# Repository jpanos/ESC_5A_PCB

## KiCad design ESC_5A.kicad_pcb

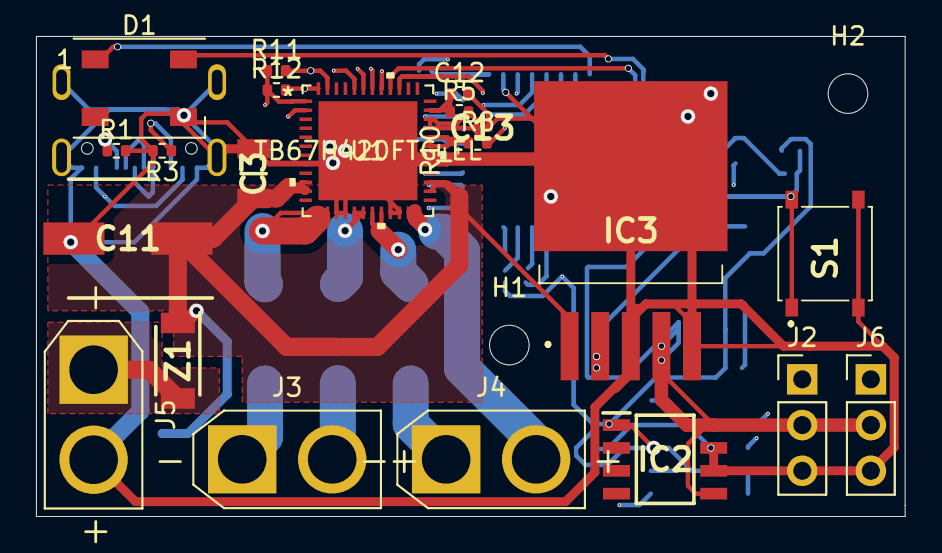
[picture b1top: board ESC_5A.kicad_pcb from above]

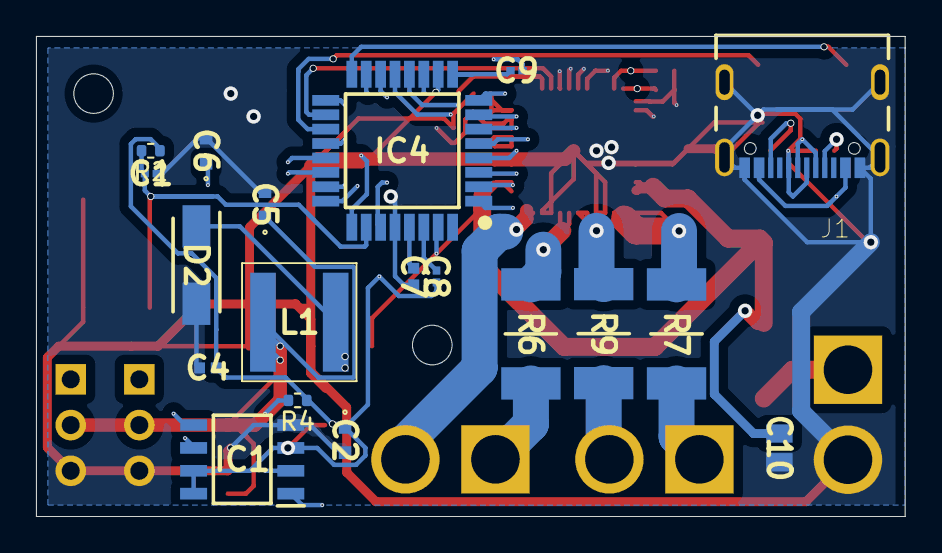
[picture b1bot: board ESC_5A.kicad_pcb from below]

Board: 4 copper layers, 48.3 x 26.7 mm, 43 parts (19 on the bottom side), 41 nets.

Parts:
C1, C8, C9, C13: .1uF; CAPC0603X33N
C2, C5, C6: 10uF; C1608_Commercial
C3: 10uF; CAPC3216X180N
C4, C7: 1uF; CAPC1005X55N
C10: .1uF; CAPC2012X110N
C11: 100uF; CAPAE660X800N
C12: 270pF; C_0402_1005Metric
D1: WS2812B; LED_WS2812B_PLCC4_5.0x5.0mm_P3.2mm
D2: B340AE-13; DIOM5226X240N
H1, H2: MountingHole; MountingHole_2.2mm_M2
IC1: EEPROM; SOIC127P600X175-8N
IC2: 3.3V Reg; SOIC127P600X170-8N
IC3: 5V_Reg; AP1501A50K5G13
IC4: ATSAMD21E17D-AUT; QFP80P900X900X120-32N
J1: USBc; GCT_USB4105-GF-A
J2, J6: 5V_PWR; PinHeader_1x03_P2.54mm_Vertical
J3: M1; AMASS_XT30U-M_1x02_P5.0mm_Vertical
J4: M2; AMASS_XT30U-M_1x02_P5.0mm_Vertical
J5: PWR_IN; AMASS_XT30U-M_1x02_P5.0mm_Vertical
L1: 33uH; XAL6060333MEC
R1, R3, R4, R5: 5.1k; R_0402_1005Metric
R2: 100k; R_0402_1005Metric
R6, R7, R9: .01; RESC6430X66N
R8: 20k; R_0402_1005Metric
R10: 5k; R_0402_1005Metric
R11, R12: 10k; R_0402_1005Metric
S1: PTS526_SK15_SMTR2_LFS; PTS526SK15SMTR2LFS
U1: TB67H420FTG_EL
Z1: SZMMSZ4713T1G; SODFL4724X108N

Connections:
+3V3: C2.1, C4.1, C8.1, C9.1, IC1.3, IC1.7, IC1.8, IC2.1, R2.1, R4.1
+5V: C5.1, C6.1, IC2.5, IC2.8, IC3.4, J1.A4_B9, J1.B4_A9, J2.2, J6.2, L1.2
ADC_1: IC4.8, J3.1, R7.2
ADC_2: IC4.6, J4.1, R6.2
ADC_3: IC4.7, J3.2, R9.2
ADC_MUX_GND: IC4.3, R9.1, U1.17, U1.18
ADC_VREFA: IC4.4, R7.1, U1.13, U1.14
ADC_VREFB: IC4.5, R6.1, U1.19, U1.20
CS_EEPROM: IC1.1, IC4.11, R4.2
D+: IC4.24, J1.A6, J1.B6
D-: IC4.23, J1.A7, J1.B7
GND: C1.1, C2.2, C3.2, C4.2, C5.2, C6.2, C7.2, C10.2, C11.2, C12.2, C13.1, D1.3, D2.2, IC1.4, IC2.6, IC2.7, IC3.3, IC3.5, IC3.6, IC4.10, IC4.28, J1.A1_B12, J1.B1_A12, J1.S1, J1.S2, J1.S3, J1.S4, J2.3, J5.2, J6.3, R1.2, R3.2, R10.1, S1.3, S1.4, U1.8, U1.15, U1.16, U1.21, U1.22, U1.29, U1.30, U1.49
HBMODE: IC4.25, U1.2
INA1: IC4.15, U1.41
INA2: IC4.14, U1.42
INB1: IC4.13, U1.43
INB2: IC4.12, U1.44
LO1: IC4.1, R11.2, U1.47
LO2: IC4.2, R12.2, U1.48
MISO_EEPROM: IC1.2, IC4.20
MOSI_EEPROM: IC1.5, IC4.22
MotorB_Neg: J4.2, U1.23, U1.24
NRST: C1.2, IC4.26, R2.2, S1.1, S1.2
unnamed: C7.1, IC4.29
unnamed: C8.2, IC4.30
unnamed: C9.2, IC4.9
unnamed: D2.1, IC3.2, L1.1
unnamed: J1.A5, R1.1
unnamed: J1.B5, R3.1
OSCM: C12.1, R5.1, U1.35
PPM_1: IC4.27, J2.1
PPM_2: IC4.31, J6.1
PWMA: IC4.17, U1.39
PWMB: IC4.18, U1.40
PWR: C3.1, C10.1, C11.1, IC3.1, U1.10, U1.11, U1.26, U1.27, Z1.1
PWR_IN: J5.1, Z1.2
RGB_DATA: D1.4, IC4.19
RGB_PWR: D1.1, IC4.16
SCK_EEPROM: IC1.6, IC4.21
TBLKAB: C13.2, R5.2, R8.2, R11.1, R12.1, U1.1, U1.33, U1.34
VREF: R8.1, R10.2, U1.31, U1.32

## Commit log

2021-06-18 Inital Commit
2021-06-18 adding driver
2021-06-18 EOD fri
2021-06-21 New Driver and rev_1 Schemetic. not including custom monitforing
2021-06-21 leaving office
2021-06-22 Schematic Rev_One Done pre review
2021-06-23 Layout Rev_One done need to revise to shrink board
2021-06-25 Smaller board Created but fears of the issues with GND connections
2021-06-25 Added M2 mounting holes and cleaned solder mask
2021-06-25 labeled
2021-06-25 feather profile
2021-06-25 Leaving work for remote work
2021-07-01 Remote work
2021-07-01 Finsihed rev one layout.. size too big
2021-07-01 Converted everything to XT30
2021-07-01 testing other options
2021-07-01 Rev one layout
2021-07-02 Pre_layout
2021-07-02 Was able to shrink board another 6mm
2021-07-02 working on layout
2021-07-02 Added second PPM input for indepedant motor control
2021-07-06 Checking on layout of driver VDD
2021-07-06 Layout Rev_One done pre review
2021-07-06 pre layout
2021-07-06 Generated Gerbers
2021-07-07 Generated Gerbers on layout post review one
2021-07-07 removed two current sense resistors and multiple unsused ADC pins
2021-07-08 Waiting on 4 layer results
2021-07-12 Finalized Gerbers sent to PCBWAY for inital prototype production
2021-07-12 cleaning up outdated files

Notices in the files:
parts and their libraries:
Copyright 2021 Accelerated Designs. All rights reserved.
